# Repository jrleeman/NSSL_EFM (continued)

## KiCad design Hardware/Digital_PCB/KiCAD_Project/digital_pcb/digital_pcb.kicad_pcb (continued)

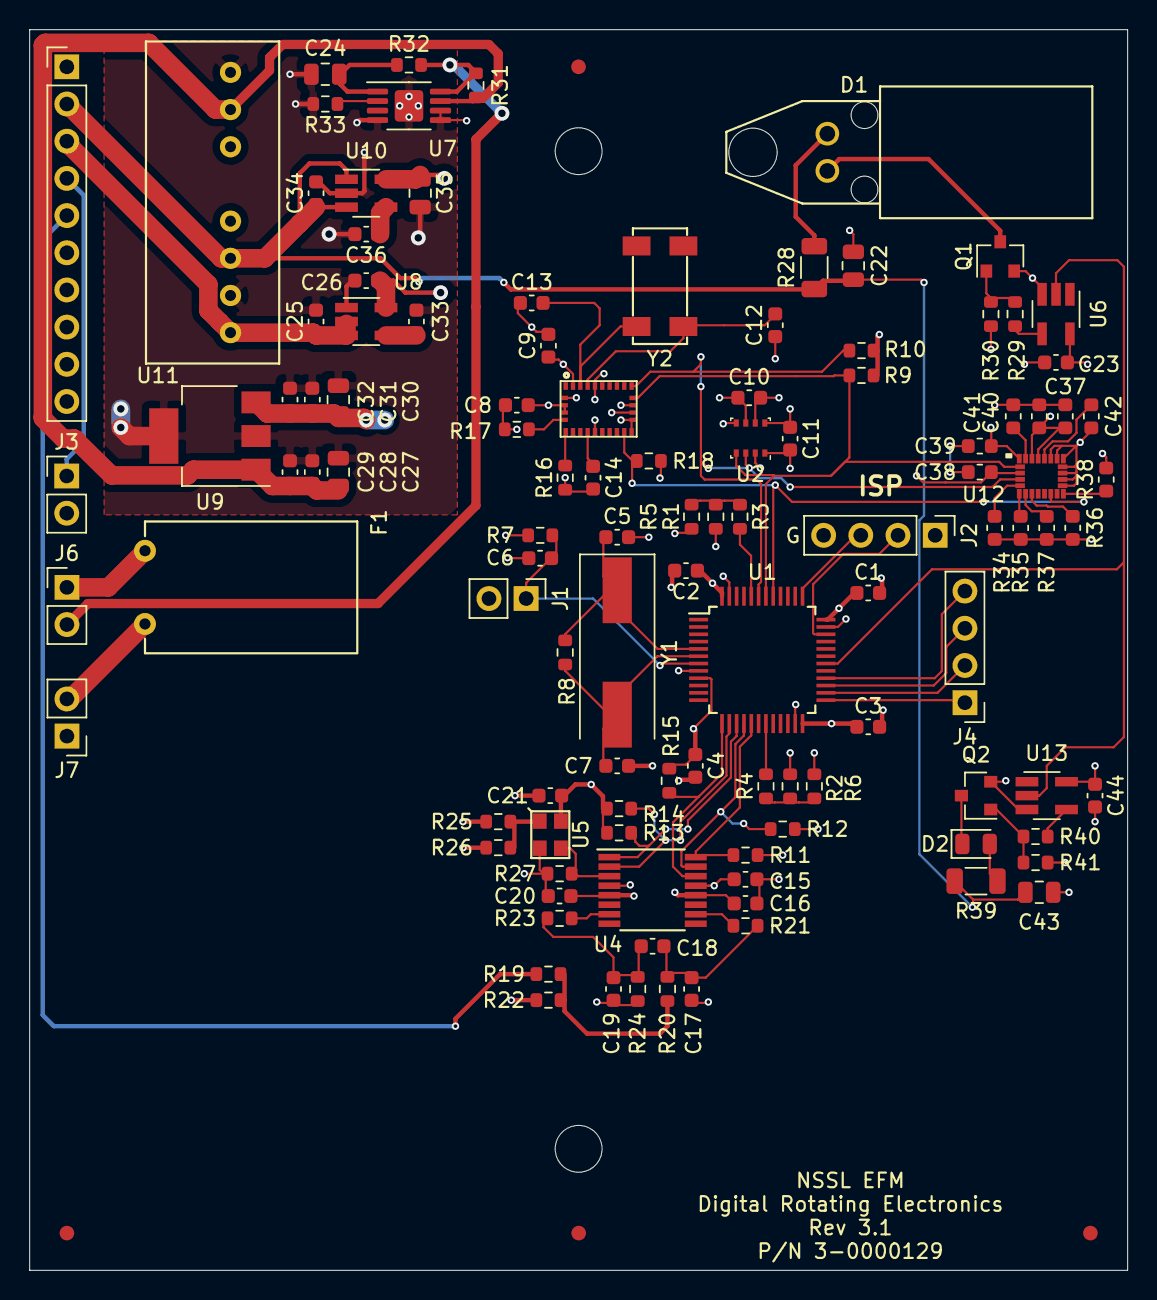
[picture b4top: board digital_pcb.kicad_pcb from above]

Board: 4 copper layers, 75.0 x 84.8 mm, 119 parts (0 on the bottom side), 65 nets.

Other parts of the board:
C37, C38, C39, C40, C41: 1-0000007
C42: 1-0000014
R34, R35, R36, R37: 1-0000010
R38: 1-0000006
U12: 1-0000925

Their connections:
+3V3: C37.2, C38.2, C39.2, C40.2, R34.1, R35.1, R36.1, R37.1, R38.2, U12.1, U12.3, U12.22, U12.23; also elsewhere on the board
GND: C37.1, C38.1, C39.1, C40.1, C41.1, C42.1, U12.14, U12.15, U12.16, U12.17, U12.18, U12.19, U12.20; also elsewhere on the board
I2C_SCL: U12.2; also elsewhere on the board
I2C_SDA: U12.4; also elsewhere on the board
IMU_INT: U12.11; also elsewhere on the board
unnamed: C41.2, U12.24
unnamed: C42.2, U12.21
unnamed: R34.2, U12.5
unnamed: R35.2, U12.6
unnamed: R36.2, U12.8
unnamed: R37.2, U12.7
unnamed: R38.1, U12.13

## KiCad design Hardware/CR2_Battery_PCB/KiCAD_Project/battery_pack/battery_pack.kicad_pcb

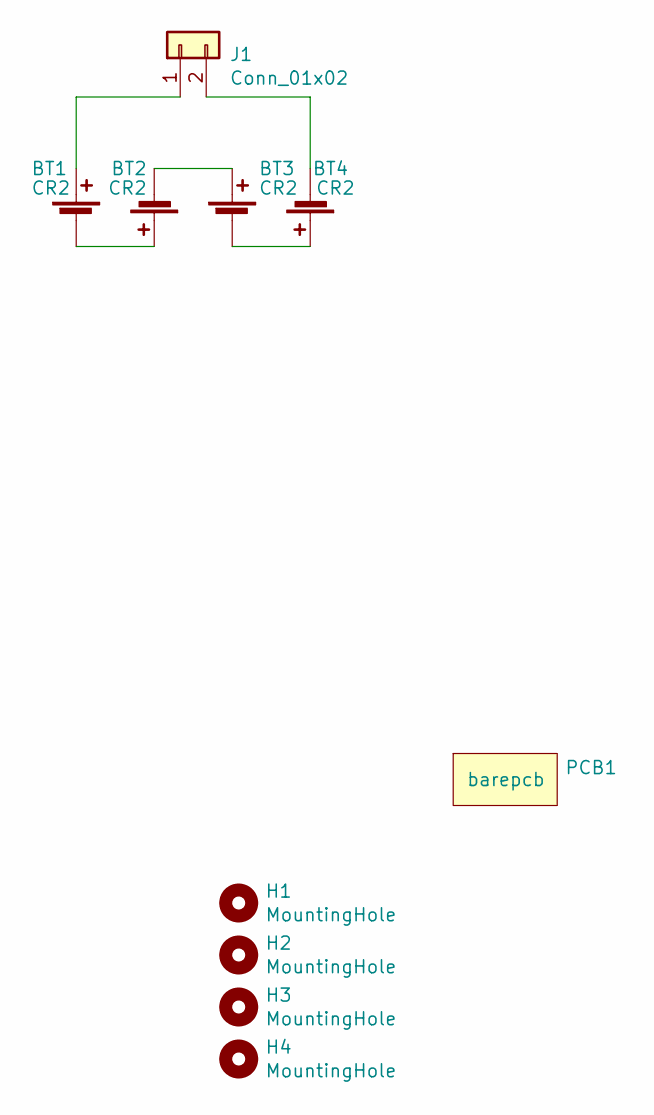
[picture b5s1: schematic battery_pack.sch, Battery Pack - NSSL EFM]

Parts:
BT1, BT2, BT3, BT4: CR2; BH-CR2-PC
H1, H2, H3, H4: MountingHole; MountingHole_3.2mm_M3_ISO7380
J1: Conn_01x02; Pin_Header_Straight_1x02_Pitch2.54mm
PCB1: barepcb

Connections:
unnamed: BT1.1 (+), J1.1
unnamed: BT1.2 (-), BT2.1 (+)
unnamed: BT2.2 (-), BT3.1 (+)
unnamed: BT3.2 (-), BT4.1 (+)
unnamed: BT4.2 (-), J1.2

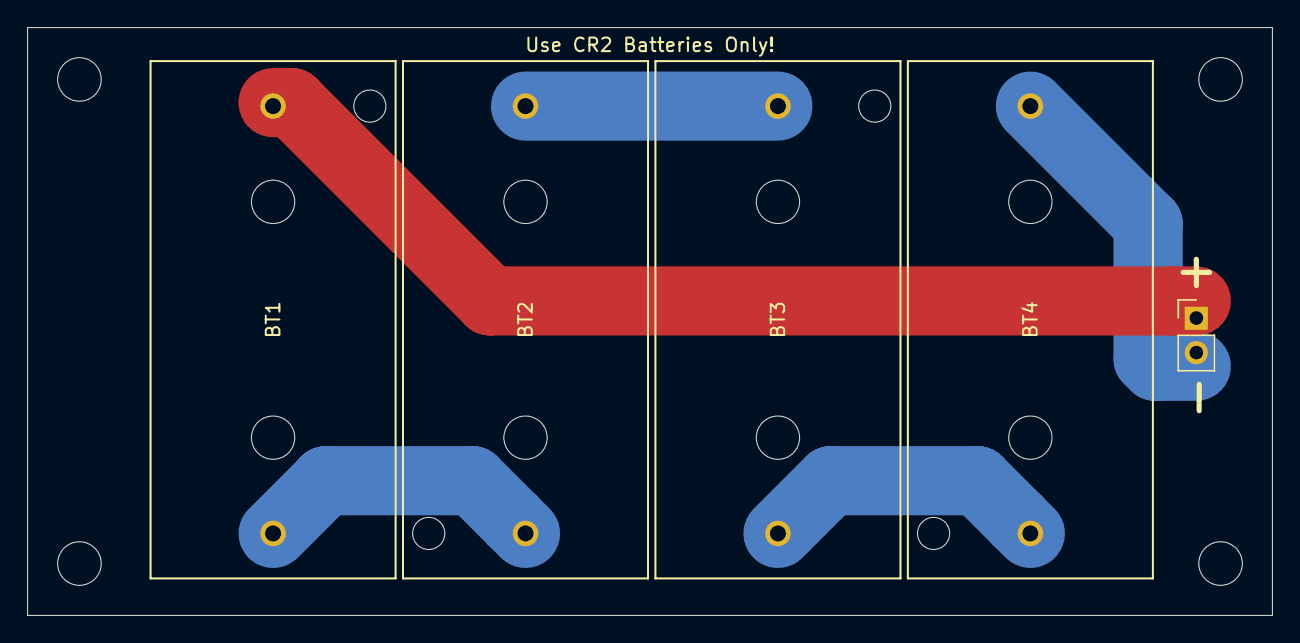
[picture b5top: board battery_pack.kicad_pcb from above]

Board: 2 copper layers, 91.4 x 43.2 mm, 10 parts (0 on the bottom side), 5 nets.

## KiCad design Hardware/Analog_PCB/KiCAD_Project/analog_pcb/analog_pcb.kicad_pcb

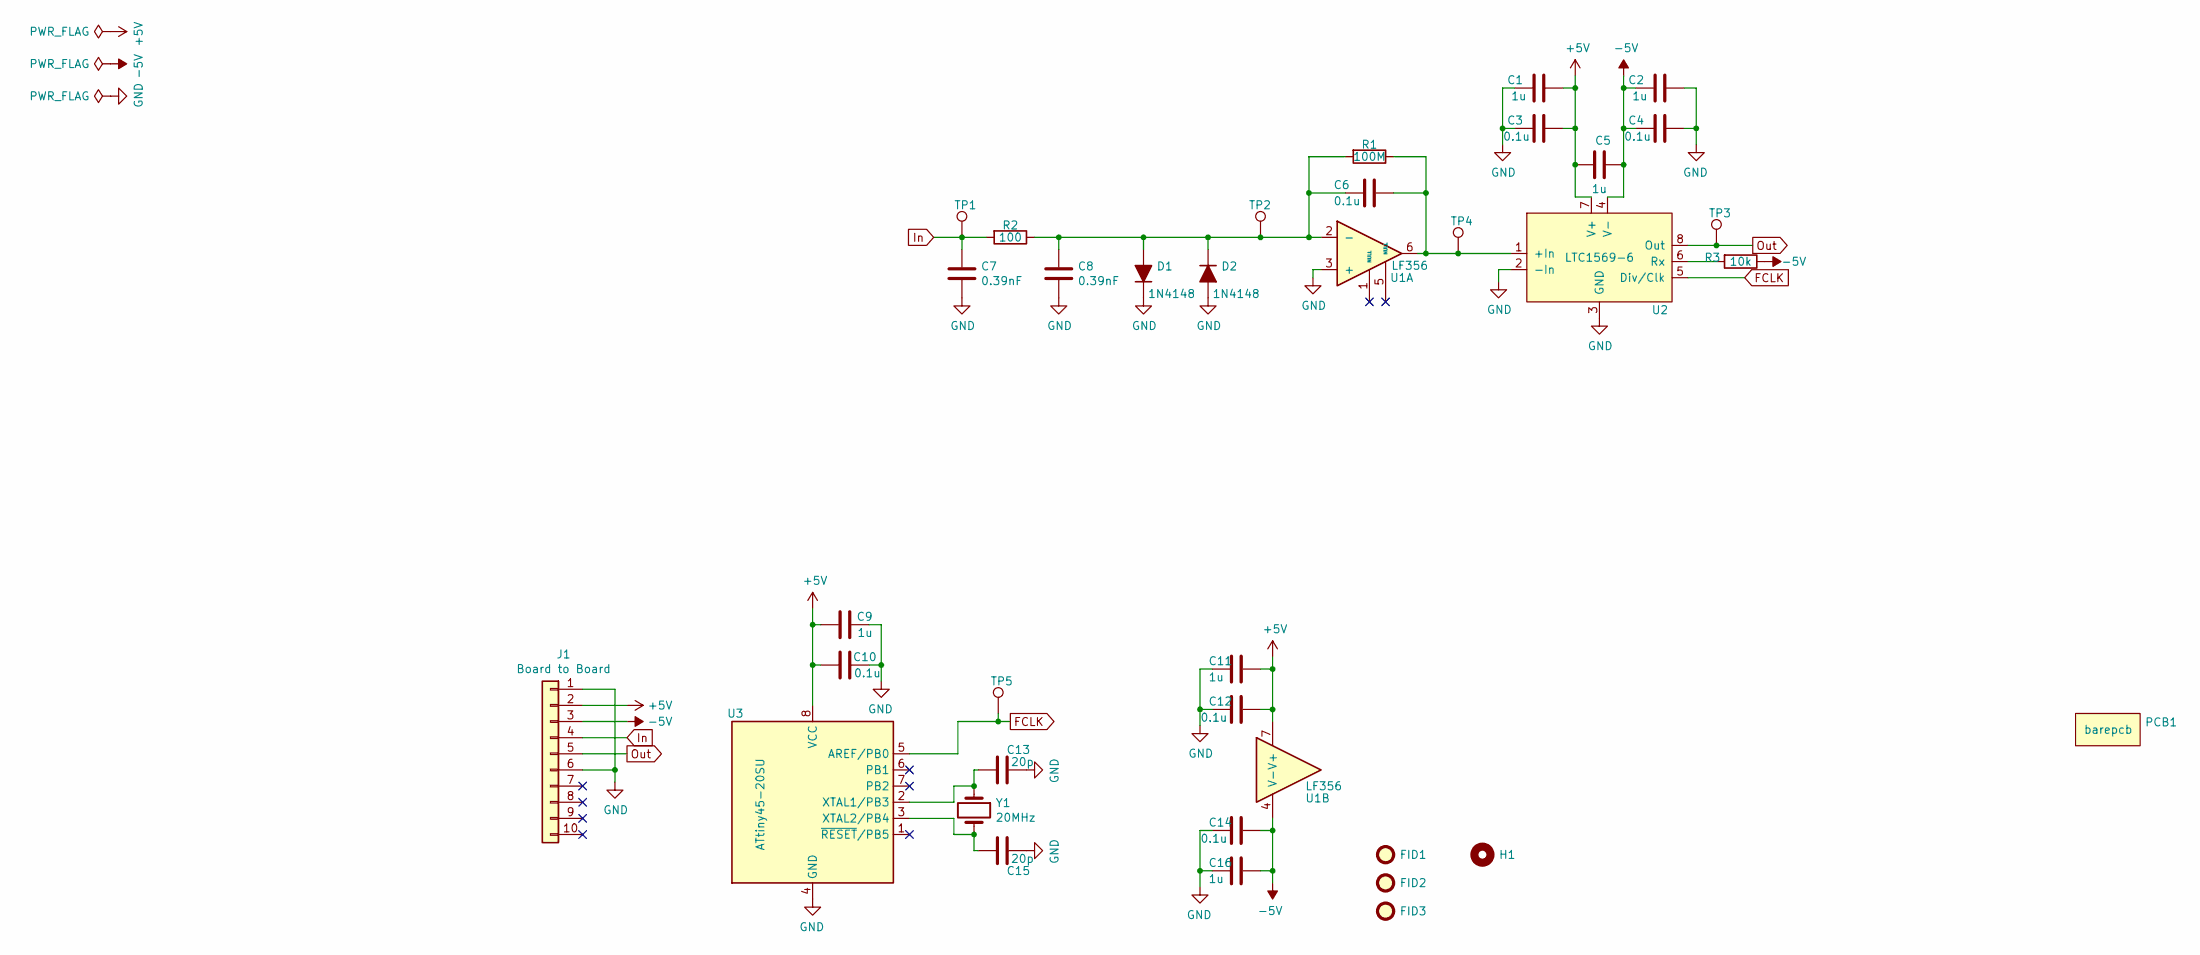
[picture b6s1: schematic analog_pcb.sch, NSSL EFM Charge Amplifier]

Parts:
C1, C2, C5, C9, C11, C16: 1u; C_0603_1608Metric
C3, C4, C10, C12, C14: 0.1u; C_0603_1608Metric
C6: 0.1u; 1-0000787
C7, C8: 0.39nF; C_0603_1608Metric
C13, C15: 20p; C_0603_1608Metric
D1, D2: 1N4148; D_SOD-323F
FID1, FID2, FID3: Fiducial; Fiducial_1mm_Dia_2mm_Outer
H1: MountingHole; MountingHole_3.2mm_M3_ISO7380
J1: Board to Board; Pin_Header_Straight_1x10_Pitch2.54mm
PCB1: barepcb
R1: 100M; R_1206_HandSoldering
R2: 100; R_0603_1608Metric
R3: 10k; R_0603_1608Metric
TP1, TP2, TP3, TP4, TP5: TestPoint; Measurement_Point_Round-SMD-Pad_Small
U1: LF356; SOIC-8_3.9x4.9mm_Pitch1.27mm
U2: LTC1569-6; SOIC-8_3.9x4.9mm_Pitch1.27mm
U3: ATtiny45-20SU; SOIC-8_5.275x5.275mm_P1.27mm
Y1: 20MHz; Crystal_HC49-U_Vertical

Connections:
+5V: C1.1, C3.1, C5.1, C9.1, C10.1, C11.1, C12.1, J1.2, U1.7 (V+), U2.7 (V+), U3.8 (VCC)
-5V: C2.2, C4.2, C5.2, C14.1, C16.1, J1.3, R3.1, U1.4 (V-), U2.4 (V-)
FCLK: TP5.1, U2.5 (Div/Clk), U3.5 (AREF/PB0)
GND: C1.2, C2.1, C3.2, C4.1, C7.2, C8.2, C9.2, C10.2, C11.2, C12.2, C13.1, C14.2, C15.1, C16.2, D1.1 (K), D2.2 (A), J1.1, J1.6, U1.3 (+), U2.2 (-In), U2.3 (GND), U3.4 (GND)
In: C7.1, J1.4, R2.2, TP1.1
unnamed: C6.1, R1.1, TP4.1, U1.6, U2.1 (+In)
unnamed: C6.2, C8.1, D1.2 (A), D2.1 (K), R1.2, R2.1, TP2.1, U1.2 (-)
unnamed: C13.2, U3.2 (XTAL1/PB3), Y1.1
unnamed: C15.2, U3.3 (XTAL2/PB4), Y1.2
unnamed: R3.2, U2.6 (Rx)
Out: J1.5, TP3.1, U2.8 (Out)

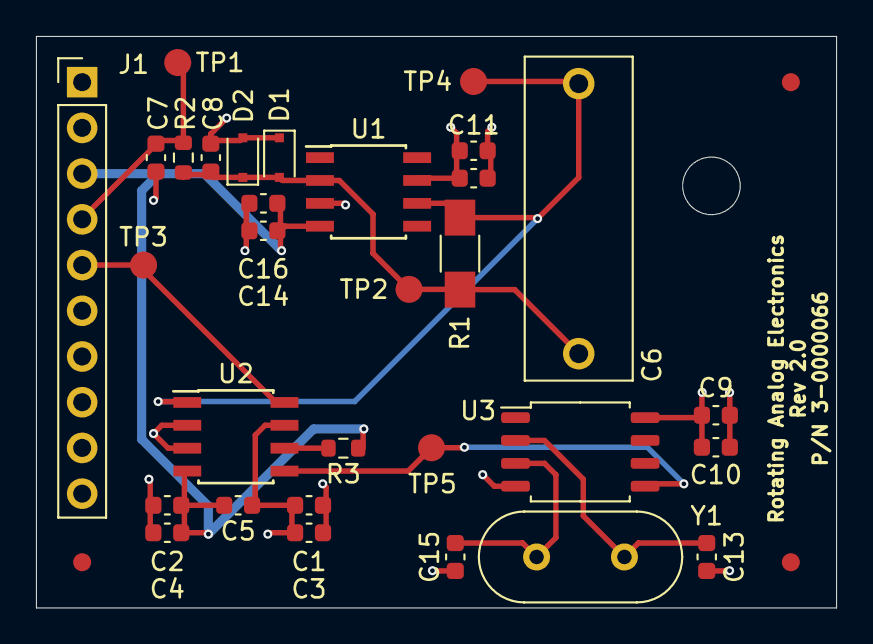
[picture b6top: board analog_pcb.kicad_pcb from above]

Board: 4 copper layers, 44.4 x 31.8 mm, 36 parts (0 on the bottom side), 11 nets.

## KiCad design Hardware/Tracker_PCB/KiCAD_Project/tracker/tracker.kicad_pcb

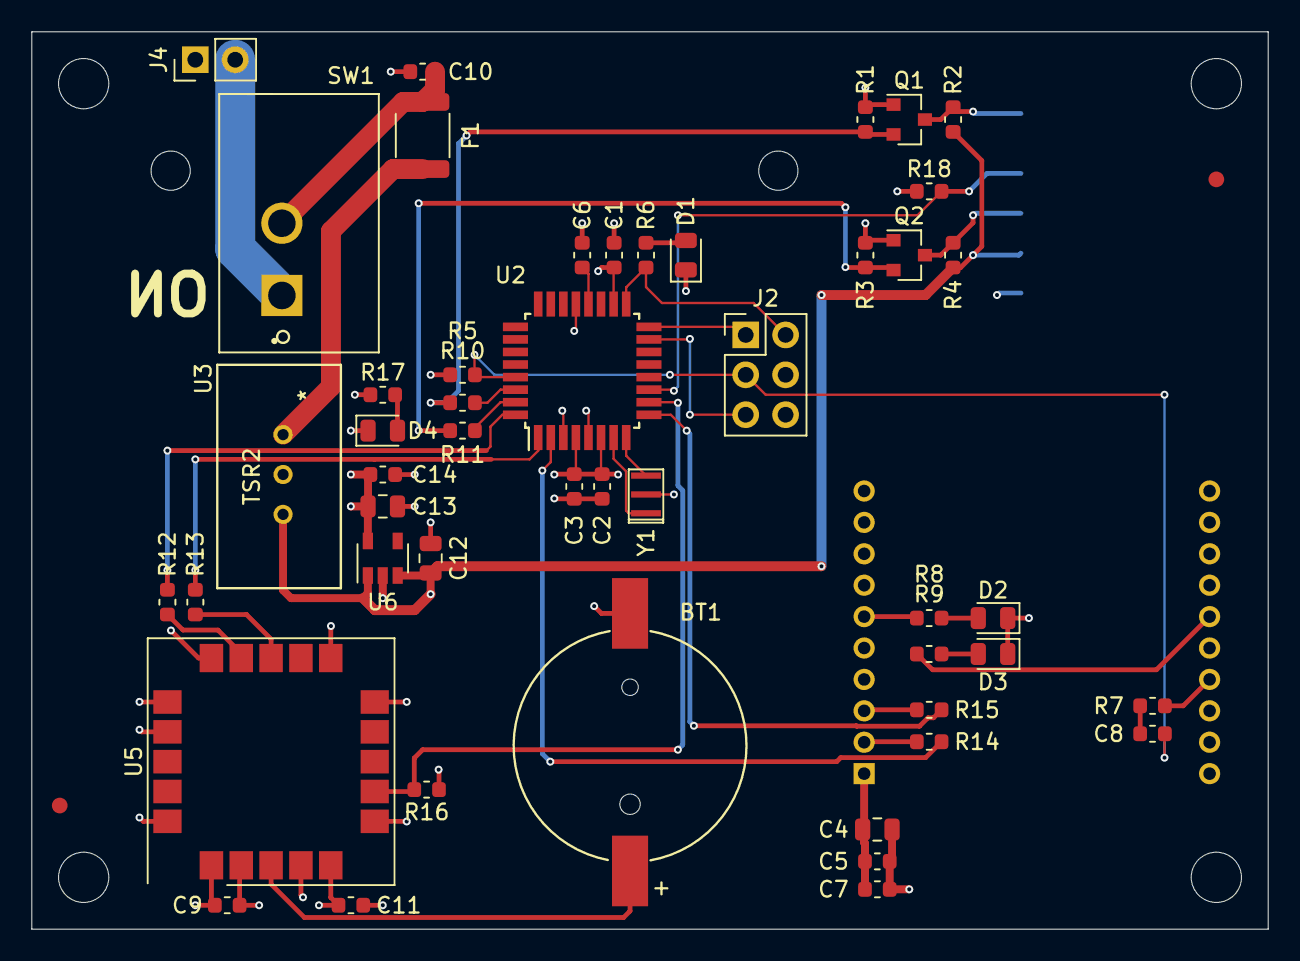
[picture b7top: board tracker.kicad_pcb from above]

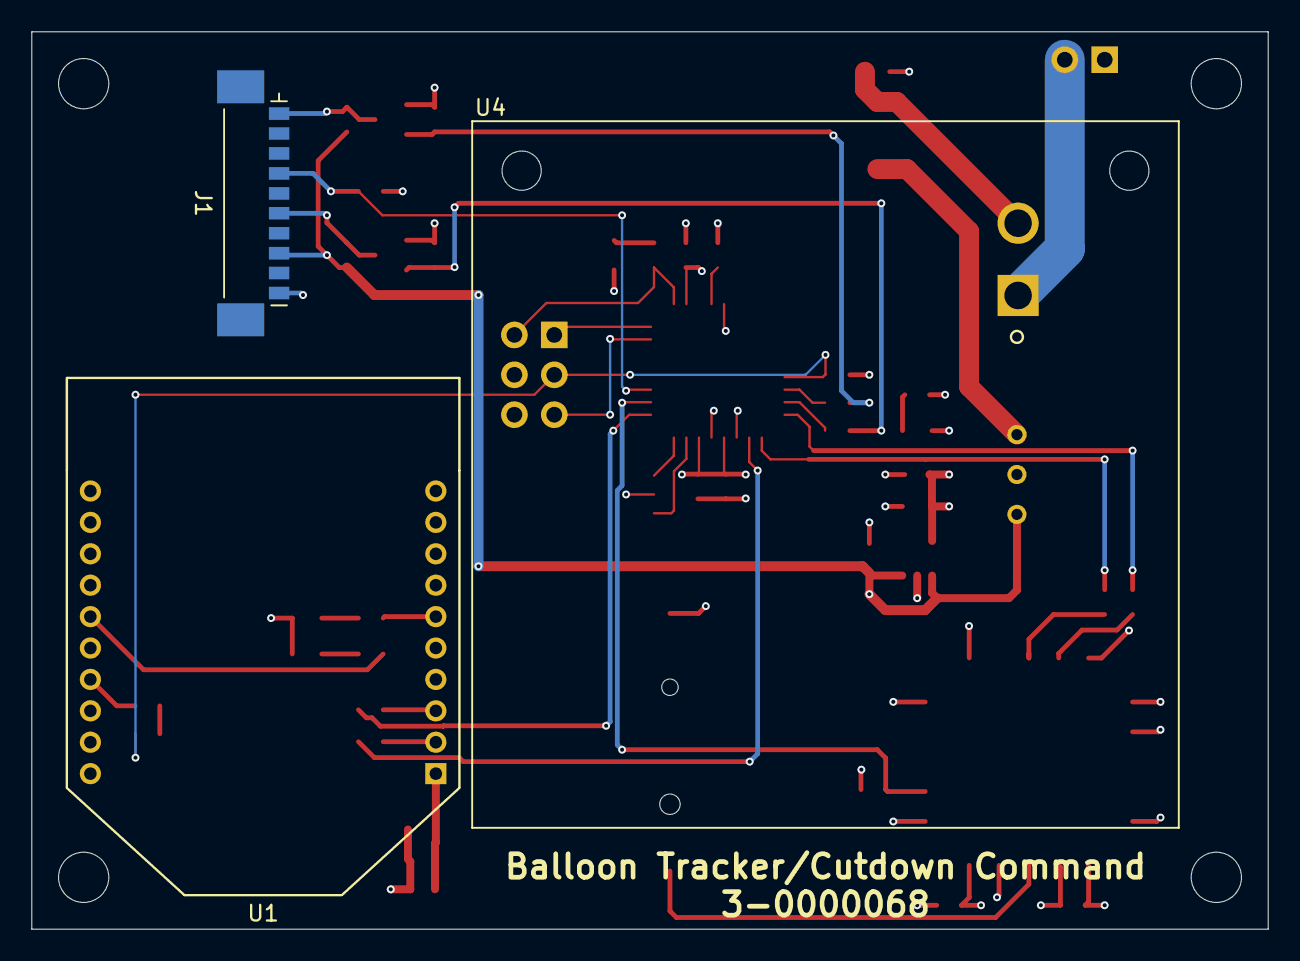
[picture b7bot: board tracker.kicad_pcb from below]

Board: 4 copper layers, 78.7 x 57.2 mm, 58 parts (3 on the bottom side), 38 nets.

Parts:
BT1: CR1220; S8411-45R
C1, C2, C3, C6, C7, C8, C9, C10, C11, C14: 1-0000007
C4, C12, C13: 1-0000075
C5: 1-0000018
D1, D2: Blue; LED_0805_2012Metric
D3: Yellow; LED_0805_2012Metric
D4: Green; LED_0805_2012Metric
F1: Polyfuse; Fuse_1812_4532Metric
FID1, FID2: Fiducial; Fiducial_1mm_Mask2mm
H1, H2, H3, H4: MountingHole; MountingHole_3.2mm_M3_DIN965
J1: RockBlock9603; picoblade
J2: ICSP; PinHeader_2x03_P2.54mm_Vertical
J4: Battery; PinHeader_1x02_P2.54mm_Vertical
PCB1: barepcb; BarePCB
Q1, Q2: BSS138; SOT-23
R1, R2, R3, R4: 1-0000013
R5, R16, R18: 1-0000010
R6, R8, R9, R17: 1-0000008
R7, R10, R11, R12, R13, R14, R15: 1-0000006
SW1: SW_SPST; SW_GF-123-0054
U1: XBee
U2: ATmega328P-AU; TQFP-32_7x7mm_P0.8mm
U3: TSR2; TSR 2-2450
U4: RockBlockMechanical; RockBlock_Mechanical
U5: ublox_SAM-M8Q
U6: MIC5219-3.3YM5; SOT-23-5
Y1: 16MHz; Resonator

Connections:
+3V3: C1.1, C2.1, C3.1, C4.1, C5.1, C7.1, C9.1, C11.1, C13.1, C14.1, J2.6, Q1.1, Q2.1, R1.1, R3.1, R5.1, R16.1, R17.1, R18.1, U1.1, U2.4, U2.6, U2.18, U5.2, U5.17, U6.5
GPS_PPS: R16.2, U2.10, U5.7
GPS_RX: R12.1, U5.14
GPS_TX: R13.1, U5.13
MISO: J2.1, U2.16
MOSI: J2.5, U2.15
unnamed: BT1.1, U5.3
unnamed: C6.1, U2.20
unnamed: C8.2, R7.1
unnamed: C10.1, F1.2, SW1.2
unnamed: D1.2, R6.2
unnamed: D2.2, R8.2
unnamed: D3.2, R9.2
unnamed: D4.2, R17.2
unnamed: F1.1, U3.1
unnamed: J4.2, SW1.1
unnamed: R7.2, U1.17
unnamed: R8.1, U1.6
unnamed: R9.1, U1.15
unnamed: R10.2, U2.30
unnamed: R11.2, U2.31
unnamed: R12.2, U2.32
unnamed: R13.2, U2.1
unnamed: R14.2, U2.2
unnamed: R15.2, U2.9
unnamed: U2.7, Y1.1
unnamed: U2.8, Y1.3
RB_5V: C12.1, J1.8, R2.1, R4.1, U3.3, U6.1, U6.3
RB_GND: BT1.2, C1.2, C2.2, C3.2, C4.2, C5.2, C6.2, C7.2, C9.2, C10.2, C11.2, C12.2, C13.2, C14.2, D1.1, D2.1, D3.1, D4.1, J1.10, J2.4, J4.1, U1.10, U2.3, U2.5, U2.21, U3.2, U5.1, U5.4, U5.5, U5.6, U5.10, U5.11, U5.15, U5.16, U5.20, U6.2, Y1.2
RB_NetAv: J1.4, R18.2, U2.11
RB_RXI: J1.6, Q2.3, R4.2
RB_RXI_3V3: Q2.2, R3.2, R11.1
RB_TXO: J1.1, Q1.3, R2.2
RB_TXO_3V3: Q1.2, R1.2, R10.1
RESET: C8.1, J2.3, R5.2, U2.29
SCK: J2.2, R6.1, U2.17
XBee_from_Uc: R15.1, U1.3
XBee_to_Uc: R14.1, U1.2

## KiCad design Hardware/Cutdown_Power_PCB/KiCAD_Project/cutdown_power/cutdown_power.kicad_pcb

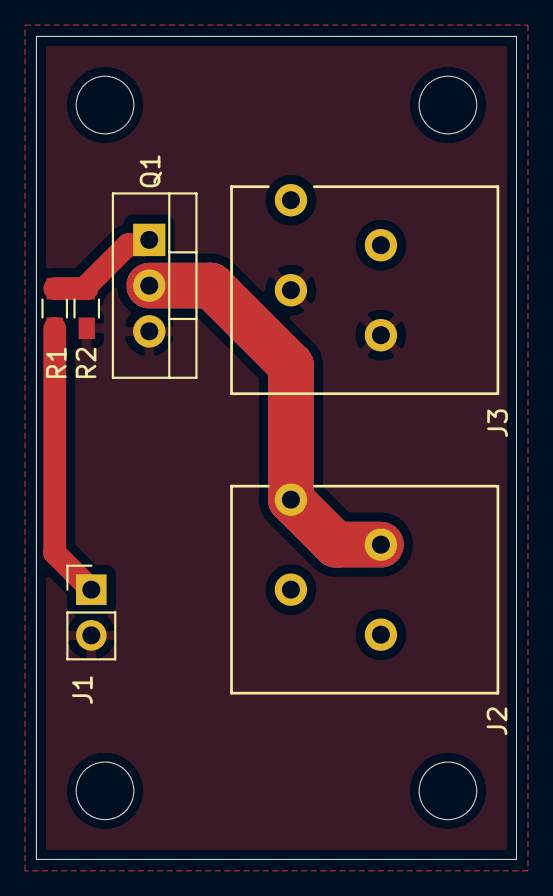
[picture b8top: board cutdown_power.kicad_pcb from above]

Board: 2 copper layers, 26.7 x 45.7 mm, 10 parts (0 on the bottom side), 5 nets.

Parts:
H1, H2, H3, H4: MountingHole; MountingHole_3.2mm_M3_ISO7380
J1: Control Signal; Pin_Header_Straight_1x02_Pitch2.54mm
J2: Heater Coil; 1986711-2
J3: Battery Pack; 1986711-2
Q1: FQP30N06L; TO-220-3_Vertical
R1: 0R0; R_0603_HandSoldering
R2: 10k; R_0603_HandSoldering

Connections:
GND: J1.2, J3.1, Q1.3, R2.2
unnamed: J1.1, R1.2
unnamed: J2.1, J3.2
unnamed: J2.2, Q1.2
unnamed: Q1.1, R1.1, R2.1

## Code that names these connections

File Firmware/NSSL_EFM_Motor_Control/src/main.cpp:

/*
 * NSSL EFM Motor Control Board
 * 
 * This board and firmware are responsible for controlling the motor speed
 * to keep the motor running at a constant RPM even as the batteries run down.
 * The rate of rotation is monitored via a hall effect sensor and magnet on the
 * rotating shaft. The average RPM over several seconds is maintained with new
 * readings being rejected a spurious if they fall outside the average.
 * 
 * The loop runs the PID controller that updates the PWM to the motor every 200ms.
 * Pulses from the hall-effect sensor trigger an ISR that determines the time that
 * revolution took at adds it to the moving average of RPM assuming that it is not
 * more than 10% different from the average. This should help eliminate any signals
 * from discharges or other random events.
 */

#include <Arduino.h>
#include <FIR.h>
#include <PID_v1.h>
#include <IWatchdog.h>
#include "pins.h"

// Globals
volatile uint16_t encoder_pulses = 0; // Counts pulses for the encoder 
char motor_cutoff_enable = 1;
char tone_system_enable = 1;
double setpoint = 120; // Target RPM for the motor
double feedback = 0; // Feedback for the motor PID
double pwm_output = 80; // Output from the PID
double pid_kp=1.0;
double pid_ki=0.1;
double pid_kd=0.0;
uint16_t motor_current_limit = 300; // mA limit before motor cutoff

// Instances
FIR<float, 4> fir;  // Since we are shooting for about 120 RPM this is a 10 second average.
PID motor_pid(&feedback, &pwm_output, &setpoint, pid_kp, pid_ki, pid_kd, REVERSE);

void EncoderISR()
{
  /*
   * Encoder ISR
   * 
   * This ISR encrements encoder pulse counts.
   */
  encoder_pulses += 1;
}

void PlayTones()
{
  /*
   * Play Tones
   * 
   * Play tones to aid in location of the instrument.
   */
    tone(PIN_BUZZER, 1000);
    delay(1000);
    tone(PIN_BUZZER, 2000);
    delay(1000);
    tone(PIN_BUZZER, 3000);
    delay(1000);
    tone(PIN_BUZZER, 4000);
    delay(1000);
    tone(PIN_BUZZER, 5000);
    delay(1000);
    noTone(PIN_BUZZER);
}

void Shutdown()
{
  /*
   * Shutdown
   * 
   * Turns off the motor, plays tones, then tries a restart of everything after ~1 minute.
   */
  analogWrite(PIN_MOTOR_PWM, 255);
  Serial.println("Shutting down.");
  if (tone_system_enable)
  {
    PlayTones();
  }
  for (uint8_t i=0; i<2; i++)
  {
    IWatchdog.reload();
    delay(20000);
  }
  IWatchdog.reload();
  while(1){} // Spin until the watchdog catches us!
}

uint16_t CurrentSafetyCheck(uint16_t current_limit_milliamps)
{
  /*
   * Current Safety Check
   * 
   * Checks the current draw of the motor and if it is over the given threshold we
   * go to the shutdown state if enabled. Otherwise return to where we were.
   */
  uint16_t voltage = 0;
  for (int i=0; i<10; i++)
  {
    voltage += analogRead(PIN_CURRENT_SENSE);
  }
  voltage /= 10;
  // Current = voltage / (Rs * Rl)
  uint16_t current = voltage * 322 / 1000;
  if ((current >= current_limit_milliamps) && motor_cutoff_enable)
  {
    Serial.print("Current limit encountered: ");
    Serial.print(current);
    Serial.println(" mA");
    Shutdown();
  }
  return current;
}

uint16_t ReadBatteryVoltage()
{
  /*
   * Read Battery Voltage
   * 
   * Check the battery voltage and return it as a number in millivolts.
   * Second multiplier is to account for the hardware voltage divider.
   */
  return analogRead(PIN_VBAT_SENSE) * 3.22656 * 3.7037;
}

void AttachEncoderInterrupt()
{
  /*
   * Start the encoder pulse counting ISR.
   */
  attachInterrupt(digitalPinToInterrupt(PIN_MOTOR_ENCODER), EncoderISR, FALLING);
}


void DetachEncoderInterrupt()
{
  /*
   * Stop the encoder pulse counting ISR.
   */
  detachInterrupt(digitalPinToInterrupt(PIN_MOTOR_ENCODER));
}


float_t CalculateRPM(uint16_t count, uint32_t start_time, uint32_t end_time)
{
  /*
   * Calculate the RPM of the motor given 6 pulses/rev and the start/end times.
   */
  return (count / 6.0) / ((end_time - start_time) / 60000);
}

float RPMCheck(uint32_t count_interval_ms)
{
  /* Checks on the RPM of the motor - if we are counting, see if we should keep counting.
   * If we are still counting, return -1. If time has elapsed, we stop counting,
   * calculate RPM, restart counting, return the RPM.
   */
  static uint32_t start_counting = millis();
  static uint32_t stop_counting = millis();

  // If it's time to do the RPM update
  if ((millis() - start_counting) >= count_interval_ms)
  {
    // Stop the interrupt, do the math
    DetachEncoderInterrupt();
    stop_counting = millis();
    float rpm = (encoder_pulses / 6.0) * ((stop_counting - start_counting) / 60000.0);
    encoder_pulses = 0;

    // Restart the interrupt
    AttachEncoderInterrupt();
    start_counting = millis();

    return rpm;
  }

  // Not time to do the update yet
  return -1;
}

void VerifyRotation()
{
  // Verify that the motor is rotating at least a little (1 pulse/100ms). Blocking.
  if (motor_cutoff_enable)
  {
   uint16_t encoder_initial = encoder_pulses;
   delay(100);
   uint16_t encoder_final = encoder_pulses;
   if ((encoder_final - encoder_initial) <= 0)
   {
     Shutdown();
   }
  }
}

void setup()
{
  /*
   * Setup
   * 
   * This runs once at boot and sets up all of the pin states, classes we'll need, etc.
   */

  IWatchdog.begin(26000000); //max 26208000

  delay(2000);  // Wait incase a user is starting a terminal
  Serial.begin(115200); // Start a serial port
  Serial.println("NSSL EFM Motor Controller");
  Serial.println("Leeman Geophysical LLC");
  Serial.println("Setting up controller...");

  // Pin Setup
  pinMode(PIN_MOTOR_ENCODER, INPUT);
  pinMode(PIN_MOTOR_DIRECTION, OUTPUT);
  pinMode(PIN_TONE_SYSTEM_ENABLE, INPUT);
  pinMode(PIN_MOTOR_CUTOFF_ENABLE, INPUT);

  
  // PID Setup
  motor_pid.SetSampleTime(9000);

  // Read the dip switch settings - this only happens once on boot!
  motor_cutoff_enable = !digitalRead(PIN_MOTOR_CUTOFF_ENABLE);
  tone_system_enable = !digitalRead(PIN_TONE_SYSTEM_ENABLE);
  
  if (motor_cutoff_enable){Serial.println("Motor Cutoff Enabled.");}
  else {Serial.println("Motor Cutoff Disabled.");}

  if (tone_system_enable){Serial.println("Tone System Enabled.");}
  else {Serial.println("Tone System Disabled.");}

  // Motor Controller Setup
  digitalWrite(PIN_MOTOR_DIRECTION, LOW);
  analogWrite(PIN_MOTOR_PWM, 10); // Start the motor
  delay(2000);

  // Make sure the current is okay after spinup
  CurrentSafetyCheck(motor_current_limit);

  IWatchdog.reload();

  // Get the RPM update method running by calling with a short interval
  RPMCheck(1000);
  delay(1100);
  RPMCheck(1000);
  delay(1100);
  // Turn on the PID
  motor_pid.SetMode(AUTOMATIC);
  Serial.println("Startup Complete");
  Serial.println("Milliseconds, Feedback, Setpoint, PWM_Output, Current_mA, Battery_mV");

}

void loop()
{
  /*
   * Main Loop
   * 
   * The main loop checks if a new rpm reading is available (interrupt has fired) and
   * updates our estimate of the feedback variable. It then calls compute on the PID
   * which will update every 200ms. On update the PWM value is updated and the parameters
   * are printed out on the serial port. We also check the current and if it is over our
   * threshold, we turn off the motor.
   */

  IWatchdog.reload();

  // Check the current draw
  uint16_t current_milliamps = CurrentSafetyCheck(motor_current_limit);

  // Check the battery voltage
  uint16_t battery_voltage = ReadBatteryVoltage();

  // Check that in 100ms we at least get 1 encoder pulse - otherwise stop!
  VerifyRotation();

  // Check if there is an update to the motor RPM
  feedback = RPMCheck(10000);
  feedback = int(feedback);

  if (feedback != -1)
  {
    motor_pid.Compute();  // Compute and update
    analogWrite(PIN_MOTOR_PWM, pwm_output);
    Serial.print(millis());
    Serial.print(",");
    Serial.print(feedback);
    Serial.print(",");
    Serial.print(setpoint);
    Serial.print(",");
    Serial.print(pwm_output);
    Serial.print(",");
    Serial.print(current_milliamps);
    Serial.print(",");
    Serial.println(battery_voltage);
  }
}

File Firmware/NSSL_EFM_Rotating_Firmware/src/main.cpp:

/*
 * NSSL EFM Rotating Module Firmware
 * 
 * This board and firmware read the electric field, temperature/humidity,
 * and orientation information and reports it via the fiber optic link to
 * the control paddle electronics.
 */

#include <Arduino.h>
#include <Wire.h>
#include "Adafruit_Sensor.h"
#include <Adafruit_LSM9DS1.h>
#include <Adafruit_BME280.h>
#include "ADS1220.h"
#include "pins.h"
#include "utility/imumaths.h"
#include <SoftwareSerial.h>

Adafruit_BME280 bme;
Adafruit_LSM9DS1 lsm = Adafruit_LSM9DS1();
ADS1220 adc;
//SoftwareSerial debugSerial(PB12, PB13); // RX, TX

void setup()
{
  // Setup serial communications
  Serial.begin(38400);
  //debugSerial.begin(19200);

  //debugSerial.println("NSSL Rotating Electronics");

  // Setup the IMU
  lsm.setupAccel(lsm.LSM9DS1_ACCELRANGE_4G);
  lsm.setupMag(lsm.LSM9DS1_MAGGAIN_4GAUSS);
  lsm.setupGyro(lsm.LSM9DS1_GYROSCALE_2000DPS);
  if(!lsm.begin())
  {
    //debugSerial.println("Error starting IMU.");
  }

  // Setup the Temperature/Humidity sensor
  if(!bme.begin(0x76, &Wire))
  {
    //debugSerial.println("Error starting BME280 sensor.");
  }

  // Setup the ADC
  adc.begin(PIN_ADC_CS, PIN_ADC_DRDY);
  // Set to normal operating mode
  adc.setOpMode(0);
  // Set to continuous conversion mode
  adc.setConversionMode(1);
  // Set to 20 Hz data rate
  adc.setDataRate(0x00);
  // Use the internal 2.048V reference
  adc.setVoltageRef(0);
  // Turn off the FIR filters
  adc.setFIR(0);
  // Set gain to 1 (000)
  adc.setGain(1);
  // AIN1 is positive signal, AIN2 is negative signal
  adc.setMultiplexer(0x03);
  // Disable the PGA
  adc.setPGAbypass(1);
}

void serialWrite32(uint32_t data)
{
  byte buf[4];
  buf[0] = data & 255;
  buf[1] = (data >> 8) & 255;
  buf[2] = (data >> 16) & 255;
  buf[3] = (data >> 24) & 255;
  Serial.write(buf, sizeof(buf));
}

void serialWriteuint16(uint16_t data)
{
  byte buf[2];
  buf[0] = data & 255;
  buf[1] = (data >> 8) & 255;
  Serial.write(buf, sizeof(buf));
}

void serialWriteint16(int16_t data)
{
  byte buf[2];
  buf[0] = data & 255;
  buf[1] = (data >> 8) & 255;
  Serial.write(buf, sizeof(buf));
}

void loop()
{
  static uint8_t loop_counter = 0;
  static int16_t temperature_degC = 0;
  static uint16_t relative_humidity = 0;
  static uint16_t pressure_pa = 0;

  while (!adc.isDataReady()){} // Spin until we have new data

  // Get the time closest to when we have data ready
  uint32_t adc_ready_time = millis();

  // Read the IMU as close to the ADC time as possible
  lsm.read();

  // Read the ADC
  uint32_t adc_reading = adc.readADC();

  // Read the temperature or humidity - this is a very primitive scheduler that keeps things
  // fast enough that we can sample as fast as we want.
  if (loop_counter == 0)
  {
    relative_humidity = bme.readHumidity();
  }

  if (loop_counter == 25)
  { 
    pressure_pa = bme.readPressure() / 10;
  }

  if (loop_counter == 50)
  {
    temperature_degC = bme.readTemperature() * 10;
  }
  
  Serial.write(0xBE);  // Packet Byte 0
  serialWrite32(adc_ready_time);  // Packet Byte 1-4
  serialWrite32(adc_reading);  // Packet Byte 5-8
  serialWriteint16((int16_t)lsm.magData.x);  // Packet Byte 9-10
  serialWriteint16((int16_t)lsm.magData.y);  // Packet Byte 11-12
  serialWriteint16((int16_t)lsm.magData.z);  // Packet Byte 13-14
  serialWriteint16((int16_t)lsm.gyroData.x);  // Packet Byte 15-16
  serialWriteint16((int16_t)lsm.gyroData.y);  // Packet Byte 17-18
  serialWriteint16((int16_t)lsm.gyroData.z);  // Packet Byte 19-20
  serialWriteint16((int16_t)lsm.accelData.x);  // Packet Byte 21-22  
  serialWriteint16((int16_t)lsm.accelData.y);  // Packet Byte 23-24
  serialWriteint16((int16_t)lsm.accelData.z);  // Packet Byte 25-26
  serialWriteint16(temperature_degC);  // Packet Byte 27-28
  serialWriteuint16(relative_humidity); // Packet Byte 29-30
  serialWriteuint16(pressure_pa); // Packet Byte 31-32
  Serial.write(0xEF); // Packet Byte 33

  loop_counter += 1;
  if (loop_counter == 100)
  {
    loop_counter = 0;
  }
}

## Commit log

2019-12-06 Initial design of battery pack PCB
2019-12-06 Initial design of cutdown control PCB.
2019-12-06 Initial design of cutdown power PCB.
2019-12-06 Initial design of motor control PCB.
2019-12-06 Initial design of the control PCB.
2019-12-30 Draft of rotating analog electronics.
2019-12-30 Control PCB Rev 1.0 complete.
2019-12-30 Cutdown PCB Rev 1.0 Complete.
2019-12-30 Update part numbers. Motor control Rev 1.0 complete.
2019-12-30 Digital rotating electronics draft complete.
2019-12-30 Add production zip.
2019-12-30 Add pullups and divider for ADC input.
2019-12-31 Fix reversed Q1 issue and cut Rev 1.1
2020-01-01 Analog PCB Rev 1.0 complete.
2020-01-01 Digital PCB Rev 1.0 complete.
2020-01-01 Motor control firmware draft complete.
2020-03-30 Get updated with current status.
2020-03-30 Fix GPS connection to particle.
2020-03-31 Fix flipped fiber transmtter footprint, closes #4.
2020-03-31 Update IMU crystal footprint to 4-SOJ. closes #5.
2020-03-31 Debounce power switch with load switch and RC timer. Closes #1.
2020-03-31 Update footprints for R32 and fix various small layout things and silk screen.
2020-03-31 Change to sending binary packets from the PCB
2020-03-31 Fixup DRC issues.
2020-03-31 Small production changes for rotating electronics.
2020-03-31 Add pullup to fiber optic receiver. Closes #12.
2020-03-31 Fix TX2M footprint. Closes #2
2020-03-31 Change UARTS for separate radio serial.
2020-03-31 Add transmitter datasheet.
2020-03-31 Production files for digital rotating PCB.
2020-12-17 Fix power silk screen. Closes #16
2020-12-17 Swap sensor from T/RH to T/RH/P and update schematic version.
2020-12-17 Update schematic to use ATTINY for filter frequency generation.
2020-12-17 Rework cutdown schematic for version 2
2020-12-17 Update to match current development state
2020-12-17 Tweak current limits
2020-12-17 Update to match current development
2020-12-17 Bump to match current dev
2020-12-17 Add tracker draft schematic
2020-12-17 Revise analog PCB for Rev 2.0
2020-12-17 Footprints and BOM complete.
2020-12-18 Update footprints
2020-12-18 Update BOM and misc. metadata
2020-12-18 Physically layout components on PCB
2020-12-22 Initial layout
2020-12-22 Tweak schematic and PCB
2020-12-22 Add schematic PDF
2020-12-22 Tweak layout and make production files.
2020-12-22 Update metadata and BOM
2020-12-22 Remove cutdown power pcb and update cutdown design
2020-12-22 Tweaks
2020-12-22 Correct PCB pdf
2020-12-23 Update production files
2020-12-30 Draft of next layout
2020-12-30 Add final production files
2020-12-30 Add the analog firmware for the ATTINY
2020-12-30 Update firmware for BME280 sensor.
2020-12-30 Update for Rev 3.0 main processor
2020-12-30 Set pin modes
2020-12-30 Add XBee processor firmware
2020-12-30 Add Control SD Processor Firmware
2020-12-31 Add tracker firmware
2020-12-31 Add cutdown firmware
2020-12-31 Add temp/backup files from KiCAD
2021-02-13 Tracker hardware updates
2021-02-13 Cutdown hardware updates
2021-02-13 Analog PCB hardware updates
2021-02-13 Control PCB hardware updates
2021-02-13 Digital PCB hardware updates
2021-02-13 Analog firmware for ATTINY frequency generator
2021-02-13 Cutdown firmware
2021-02-13 Update rotating firmware for next PCB rev.
2021-02-13 Motor firmware tweaks
2021-02-13 Sat Tracker Firmware
2021-03-31 Fix incorrect crystal part numbers and add production files for Rev 3.0
2021-03-31 Get firmware up to current working state
2021-03-31 Fix footprint for ATTINY
2021-03-31 Change PN for header to plug into analog PCBA.
2021-04-02 Change to 8MHz Xtal
2021-04-02 Cache bump
2021-04-14 Switch to LSM9DS1 IMU
2021-04-19 Add Analog PCB REV 2.1 files
2021-09-28 Change out cmd library for one with overrun protection and fix arming bug
2021-10-25 Make SD card write interval sensible (about 5 minutes)
2021-10-25 Simplify XBee feedthrough
2021-10-25 Minor fixes to firmware for cutdown
2021-10-25 Make master control firmware work sensibly
2021-10-25 Update PID and overcurrent parameters per testing on an EFM
2021-10-25 Improve tracker performance
2021-10-25 Add hex file
2021-11-03 Remove fake data programs and tweak motor current limits
2021-11-03 Add CR123 battery PCB
2021-11-03 Add production gerbers
2021-11-04 Move batteries, remove charging circuit, add mounting holes.
2021-11-04 Reannotate
2021-11-05 Add Arm LED and improve board layout
2021-11-09 Add watchdog, modify current limit, and rotation verification.
2021-11-09 Create Rev 3.1 production files
2021-11-22 Control Rev 3.1
2022-02-22 Make R9 no populate. Closes #57
2022-02-22 Send temperature as signed value. Closes #44
2022-02-22 Add activity LED and another IMU footprint. Closes #49 #45
2022-03-09 Digital PCB revs
2022-03-17 Modify control firmware working on serial issue
2022-03-23 Update data types and send non-floats to save packet space
2022-03-23 Increase buffer sizes and improve efficiency.
2022-03-23 Improve efficiency
2022-03-24 reduce GPS complexity and optimize performance
2022-06-29 Bump control firmware
2022-06-29 Bump SD firmware
2022-06-29 Bump XBee Firmware
2022-06-29 Typecast Adafruit's floats (dumb!) into int16 for transmission over fiber
2022-06-29 Add PNP files and minor schematic bumps
